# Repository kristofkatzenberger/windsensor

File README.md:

# Portable Wind Sensor based on MEMS Pressure Sensors

This repository contains the design files for a portable wind sensor developed in 2025/26 at the University of Applied Sciences Technikum Wien. This project was completed as part of the Bachelor's Thesis:

"Entwicklung eines tragbaren Windsensors auf Basis von MEMS-Drucksensoren"
(Development of a Portable Wind Sensor Based on MEMS Pressure Sensors)

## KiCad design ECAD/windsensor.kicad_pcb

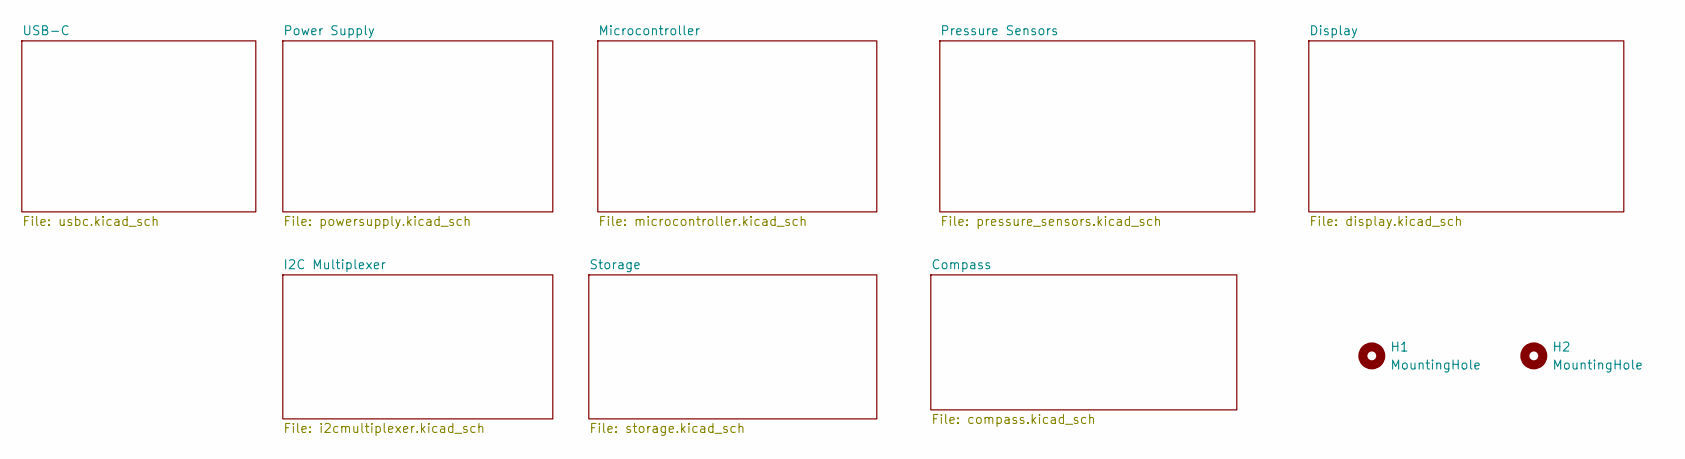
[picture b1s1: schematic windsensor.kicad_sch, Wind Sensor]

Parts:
H1, H2: MountingHole; MountingHole_3.2mm_M3

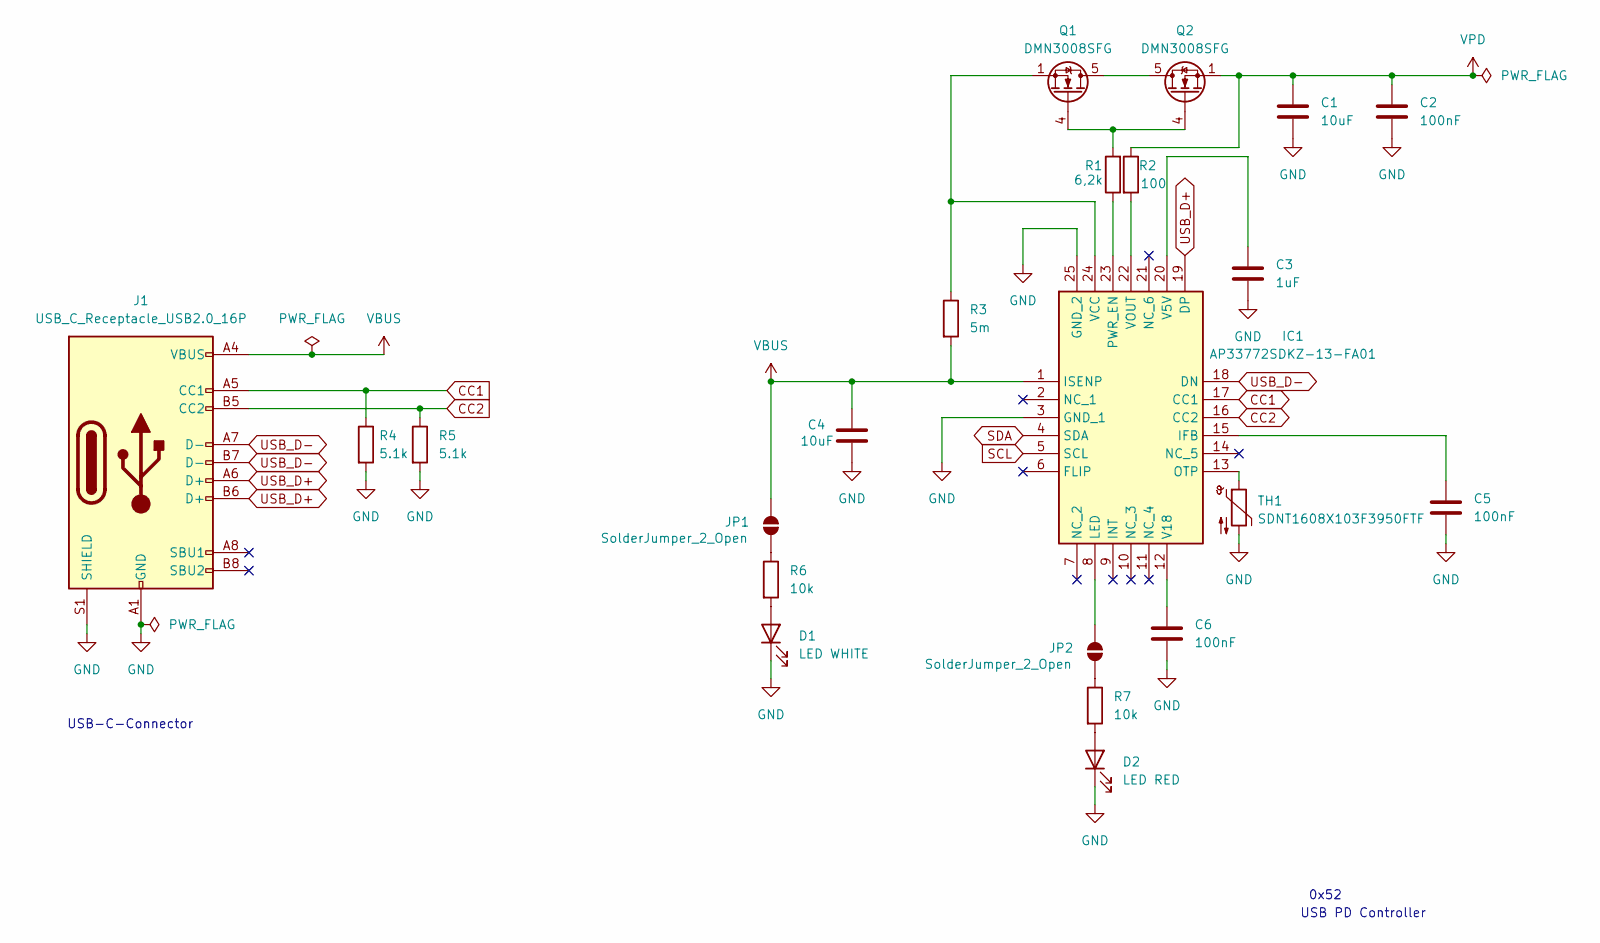
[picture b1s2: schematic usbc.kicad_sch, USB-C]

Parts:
C1, C4: 10uF; C_0402_1005Metric
C2, C5, C6: 100nF; C_0402_1005Metric
C3: 1uF; C_0402_1005Metric
D1: LED WHITE; LED_0603_1608Metric
D2: LED RED; LED_0603_1608Metric
IC1: AP33772SDKZ-13-FA01; AP33772SDKZ13FA01; Manufacturer_Part_Number AP33772SDKZ-13-FA01; Mouser Part Number 621-P33772SDKZ13FA01
J1: USB_C_Receptacle_USB2.0_16P; USB_C_Receptacle_GCT_USB4105-xx-A_16P_TopMnt_Horizontal
JP1, JP2: SolderJumper_2_Open; SolderJumper-2_P1.3mm_Open_TrianglePad1.0x1.5mm
Q1, Q2: DMN3008SFG; Diodes_PowerDI3333-8
R1: 6,2k; R_0402_1005Metric
R2: 100; R_0402_1005Metric
R3: 5m; R_1206_3216Metric; Tolerance 1%
R4, R5: 5.1k; R_0402_1005Metric
R6, R7: 10k; R_0402_1005Metric
TH1: SDNT1608X103F3950FTF; R_0603_1608Metric

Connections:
CC1: IC1.17 (CC1), J1.A5 (CC1), R4.1
CC2: IC1.16 (CC2), J1.B5 (CC2), R5.1
GND: C1.2, C2.2, C3.2, C4.2, C5.2, C6.2, D1.1 (K), D2.1 (K), IC1.3 (GND_1), IC1.25 (GND_2), J1.A1 (GND), J1.A12 (GND), J1.B1 (GND), J1.B12 (GND), J1.S1 (SHIELD), R4.2, R5.2, TH1.2; also elsewhere on the board
unnamed: D1.2 (A), R6.2
unnamed: D2.2 (A), R7.2
unnamed: C5.1, IC1.15 (IFB)
unnamed: IC1.8 (LED), JP2.1 (A)
unnamed: IC1.13 (OTP), TH1.1
unnamed: IC1.23 (PWR_EN), R1.1
unnamed: C3.1, IC1.20 (V5V)
unnamed: C6.1, IC1.12 (V18)
unnamed: IC1.24 (VCC), Q1.1 (S), Q1.2 (S), Q1.3 (S), R3.1
unnamed: IC1.22 (VOUT), R2.2
unnamed: JP1.2 (B), R6.1
unnamed: JP2.2 (B), R7.1
unnamed: Q1.5 (D), Q2.5 (D)
unnamed: Q1.4 (G), Q2.4 (G), R1.2
SCL: IC1.5 (SCL); also elsewhere on the board
SDA: IC1.4 (SDA); also elsewhere on the board
USB_D+: IC1.19 (DP), J1.A6 (D+), J1.B6 (D+); also elsewhere on the board
USB_D-: IC1.18 (DN), J1.A7 (D-), J1.B7 (D-); also elsewhere on the board
VBUS: C4.1, IC1.1 (ISENP), J1.A4 (VBUS), J1.A9 (VBUS), J1.B4 (VBUS), J1.B9 (VBUS), JP1.1 (A), R3.2
VPD: C1.1, C2.1, Q2.1 (S), Q2.2 (S), Q2.3 (S), R2.1; also elsewhere on the board

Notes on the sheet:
USB PD Controller
USB-C-Connector
0x52

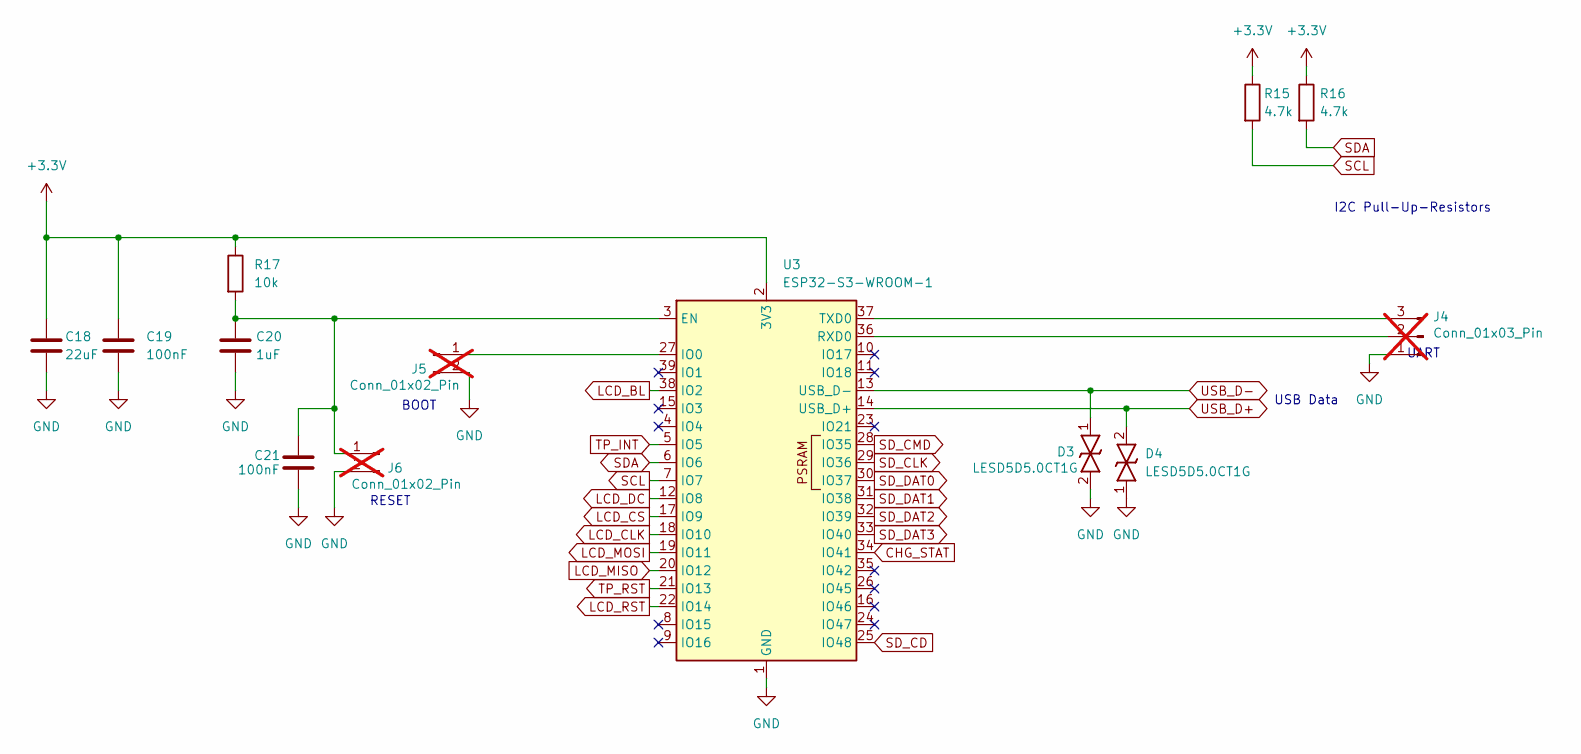
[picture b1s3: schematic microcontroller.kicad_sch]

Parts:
C18: 22uF; C_0402_1005Metric
C19, C21: 100nF; C_0402_1005Metric
C20: 1uF; C_0402_1005Metric
D3, D4: LESD5D5.0CT1G; LESD5D50CT1G; Manufacturer_Part_Number LESD5D5.0CT1G
J4: Conn_01x03_Pin; PinHeader_1x03_P2.54mm_Vertical; not fitted
J5, J6: Conn_01x02_Pin; PinHeader_1x02_P2.54mm_Vertical; not fitted
R15, R16: 4.7k; R_0402_1005Metric
R17: 10k; R_0402_1005Metric
U3: ESP32-S3-WROOM-1

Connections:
+3.3V: C18.1, C19.1, R15.1, R16.1, R17.1, U3.2 (3V3); also elsewhere on the board
CHG_STAT: U3.34 (IO41); also elsewhere on the board
GND: C18.2, C19.2, C20.2, C21.2, D3.2, D4.1, J4.1, J5.2, J6.2, U3.1 (GND), U3.40 (GND), U3.41 (GND); also elsewhere on the board
LCD_BL: U3.38 (IO2); also elsewhere on the board
LCD_CLK: U3.18 (IO10); also elsewhere on the board
LCD_CS: U3.17 (IO9); also elsewhere on the board
LCD_DC: U3.12 (IO8); also elsewhere on the board
LCD_MISO: U3.20 (IO12); also elsewhere on the board
LCD_MOSI: U3.19 (IO11); also elsewhere on the board
LCD_RST: U3.22 (IO14); also elsewhere on the board
unnamed: J4.2, U3.36 (RXD0)
unnamed: J4.3, U3.37 (TXD0)
unnamed: J5.1, U3.27 (IO0)
unnamed: C20.1, C21.1, J6.1, R17.2, U3.3 (EN)
SCL: R15.2, U3.7 (IO7); also elsewhere on the board
SDA: R16.2, U3.6 (IO6); also elsewhere on the board
SD_CD: U3.25 (IO48); also elsewhere on the board
SD_CLK: U3.29 (IO36); also elsewhere on the board
SD_CMD: U3.28 (IO35); also elsewhere on the board
SD_DAT0: U3.30 (IO37); also elsewhere on the board
SD_DAT1: U3.31 (IO38); also elsewhere on the board
SD_DAT2: U3.32 (IO39); also elsewhere on the board
SD_DAT3: U3.33 (IO40); also elsewhere on the board
TP_INT: U3.5 (IO5); also elsewhere on the board
TP_RST: U3.21 (IO13); also elsewhere on the board
USB_D+: D4.2, U3.14 (USB_D+); also elsewhere on the board
USB_D-: D3.1, U3.13 (USB_D-); also elsewhere on the board

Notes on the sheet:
I2C Pull-Up-Resistors
UART
USB Data
BOOT
RESET

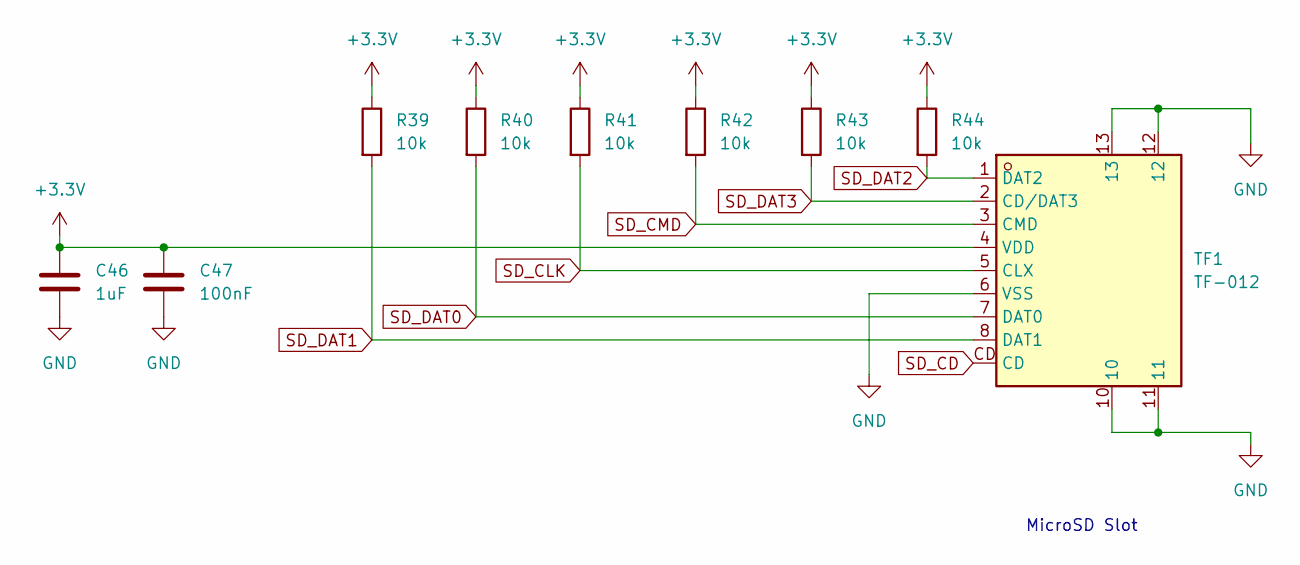
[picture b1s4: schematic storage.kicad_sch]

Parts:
C46: 1uF; C_0402_1005Metric
C47: 100nF; C_0402_1005Metric
R39, R40, R41, R42, R43, R44: 10k; R_0402_1005Metric
TF1: TF-012; TF-SMD_TF-012; Manufacturer Part TF-012; LCSC Part Name 自弹式 MicroSD卡(TF卡) 卡座

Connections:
+3.3V: C46.1, C47.1, R39.1, R40.1, R41.1, R42.1, R43.1, R44.1, TF1.4 (VDD); also elsewhere on the board
GND: C46.2, C47.2, TF1.6 (VSS), TF1.10, TF1.11, TF1.12, TF1.13; also elsewhere on the board
SD_CD: TF1.CD; also elsewhere on the board
SD_CLK: R41.2, TF1.5 (CLX); also elsewhere on the board
SD_CMD: R42.2, TF1.3 (CMD); also elsewhere on the board
SD_DAT0: R40.2, TF1.7 (DAT0); also elsewhere on the board
SD_DAT1: R39.2, TF1.8 (DAT1); also elsewhere on the board
SD_DAT2: R44.2, TF1.1 (DAT2); also elsewhere on the board
SD_DAT3: R43.2, TF1.2 (CD/DAT3); also elsewhere on the board

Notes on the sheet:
MicroSD Slot

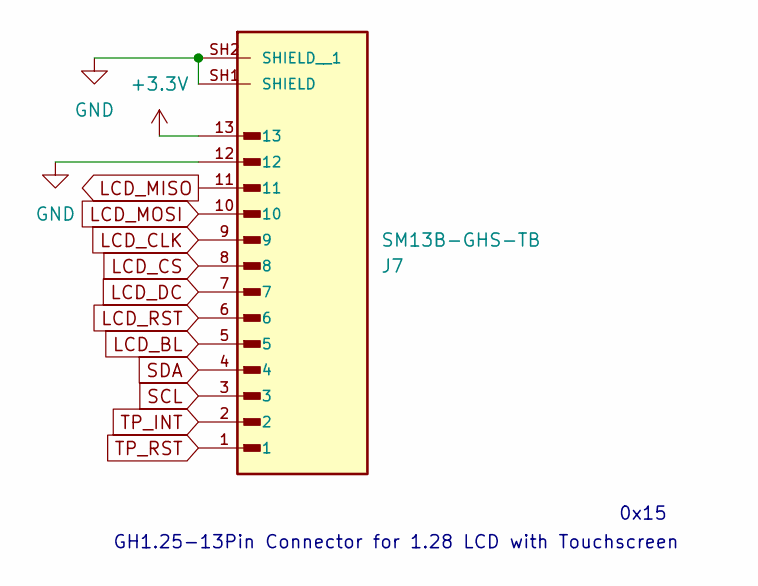
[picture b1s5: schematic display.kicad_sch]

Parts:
J7: SM13B-GHS-TB; JST_SM13B-GHS-TB; PARTREV 18/3/21

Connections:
+3.3V: J7.13; also elsewhere on the board
GND: J7.12, J7.SH1 (SHIELD), J7.SH2 (SHIELD__1); also elsewhere on the board
LCD_BL: J7.5; also elsewhere on the board
LCD_CLK: J7.9; also elsewhere on the board
LCD_CS: J7.8; also elsewhere on the board
LCD_DC: J7.7; also elsewhere on the board
LCD_MISO: J7.11; also elsewhere on the board
LCD_MOSI: J7.10; also elsewhere on the board
LCD_RST: J7.6; also elsewhere on the board
SCL: J7.3; also elsewhere on the board
SDA: J7.4; also elsewhere on the board
TP_INT: J7.2; also elsewhere on the board
TP_RST: J7.1; also elsewhere on the board

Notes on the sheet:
GH1.25-13Pin Connector for 1.28 LCD with Touchscreen
0x15

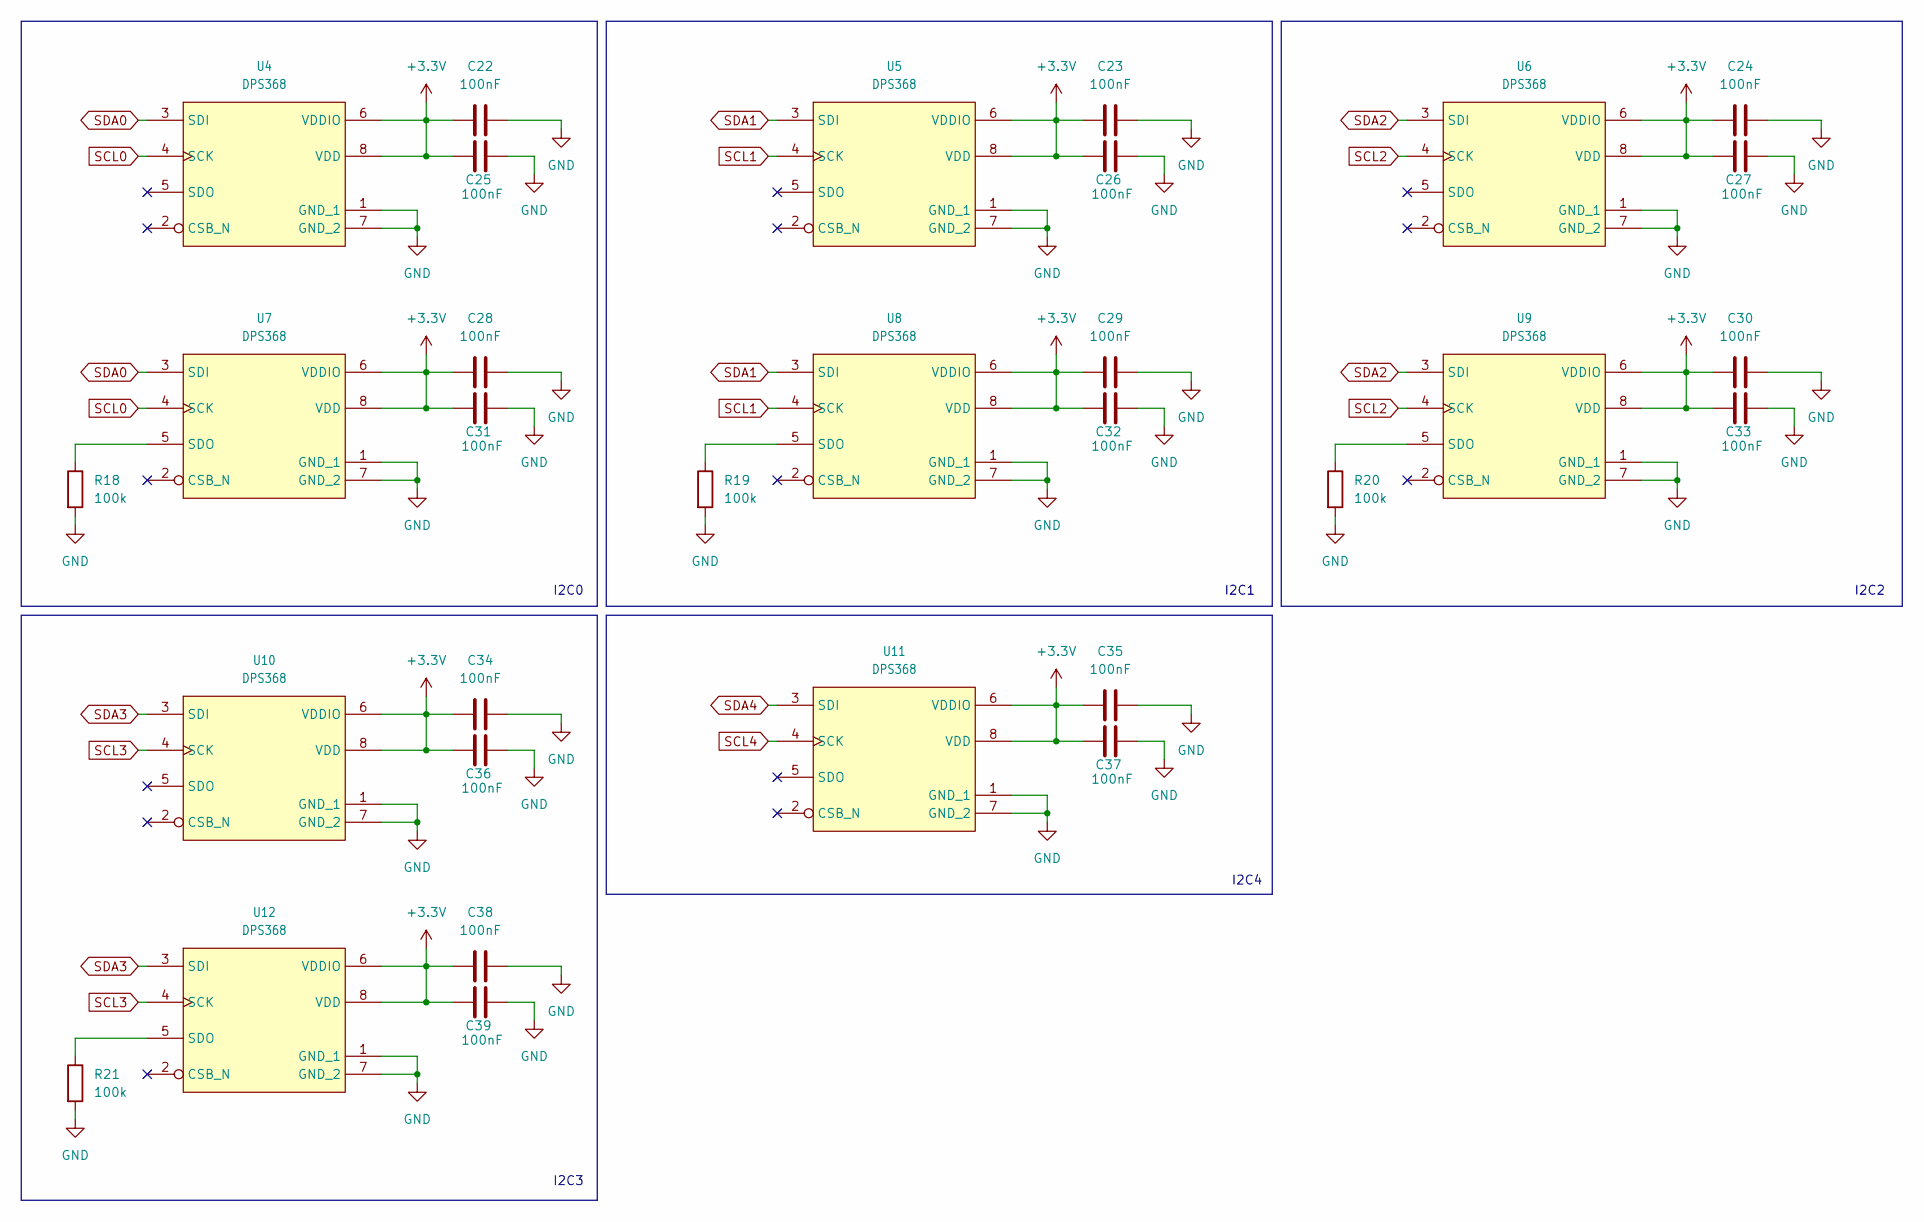
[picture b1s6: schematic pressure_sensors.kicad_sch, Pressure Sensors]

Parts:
C22, C23, C24, C25, C26, C27, C28, C29, C30, C31, C32, C33, C34, C35, C36, C37, C38, C39: 100nF; C_0402_1005Metric
R18, R19, R20, R21: 100k; R_0402_1005Metric
U4, U5, U6, U7, U8, U9, U10, U11, U12: DPS368; LGA8S145X65P2X4_200X250X110-V

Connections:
+3.3V: C22.1, C23.1, C24.1, C25.1, C26.1, C27.1, C28.1, C29.1, C30.1, C31.1, C32.1, C33.1, C34.1, C35.1, C36.1, C37.1, C38.1, C39.1, U4.6 (VDDIO), U4.8 (VDD), U5.6 (VDDIO), U5.8 (VDD), U6.6 (VDDIO), U6.8 (VDD), U7.6 (VDDIO), U7.8 (VDD), U8.6 (VDDIO), U8.8 (VDD), U9.6 (VDDIO), U9.8 (VDD), U10.6 (VDDIO), U10.8 (VDD), U11.6 (VDDIO), U11.8 (VDD), U12.6 (VDDIO), U12.8 (VDD); also elsewhere on the board
GND: C22.2, C23.2, C24.2, C25.2, C26.2, C27.2, C28.2, C29.2, C30.2, C31.2, C32.2, C33.2, C34.2, C35.2, C36.2, C37.2, C38.2, C39.2, R18.2, R19.2, R20.2, R21.2, U4.1 (GND_1), U4.7 (GND_2), U5.1 (GND_1), U5.7 (GND_2), U6.1 (GND_1), U6.7 (GND_2), U7.1 (GND_1), U7.7 (GND_2), U8.1 (GND_1), U8.7 (GND_2), U9.1 (GND_1), U9.7 (GND_2), U10.1 (GND_1), U10.7 (GND_2), U11.1 (GND_1), U11.7 (GND_2), U12.1 (GND_1), U12.7 (GND_2); also elsewhere on the board
unnamed: R18.1, U7.5 (SDO)
unnamed: R19.1, U8.5 (SDO)
unnamed: R20.1, U9.5 (SDO)
unnamed: R21.1, U12.5 (SDO)
SCL0: U4.4 (SCK), U7.4 (SCK); also elsewhere on the board
SCL1: U5.4 (SCK), U8.4 (SCK); also elsewhere on the board
SCL2: U6.4 (SCK), U9.4 (SCK); also elsewhere on the board
SCL3: U10.4 (SCK), U12.4 (SCK); also elsewhere on the board
SCL4: U11.4 (SCK); also elsewhere on the board
SDA0: U4.3 (SDI), U7.3 (SDI); also elsewhere on the board
SDA1: U5.3 (SDI), U8.3 (SDI); also elsewhere on the board
SDA2: U6.3 (SDI), U9.3 (SDI); also elsewhere on the board
SDA3: U10.3 (SDI), U12.3 (SDI); also elsewhere on the board
SDA4: U11.3 (SDI); also elsewhere on the board

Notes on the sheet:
I2C3
I2C2
I2C4
I2C1
I2C0

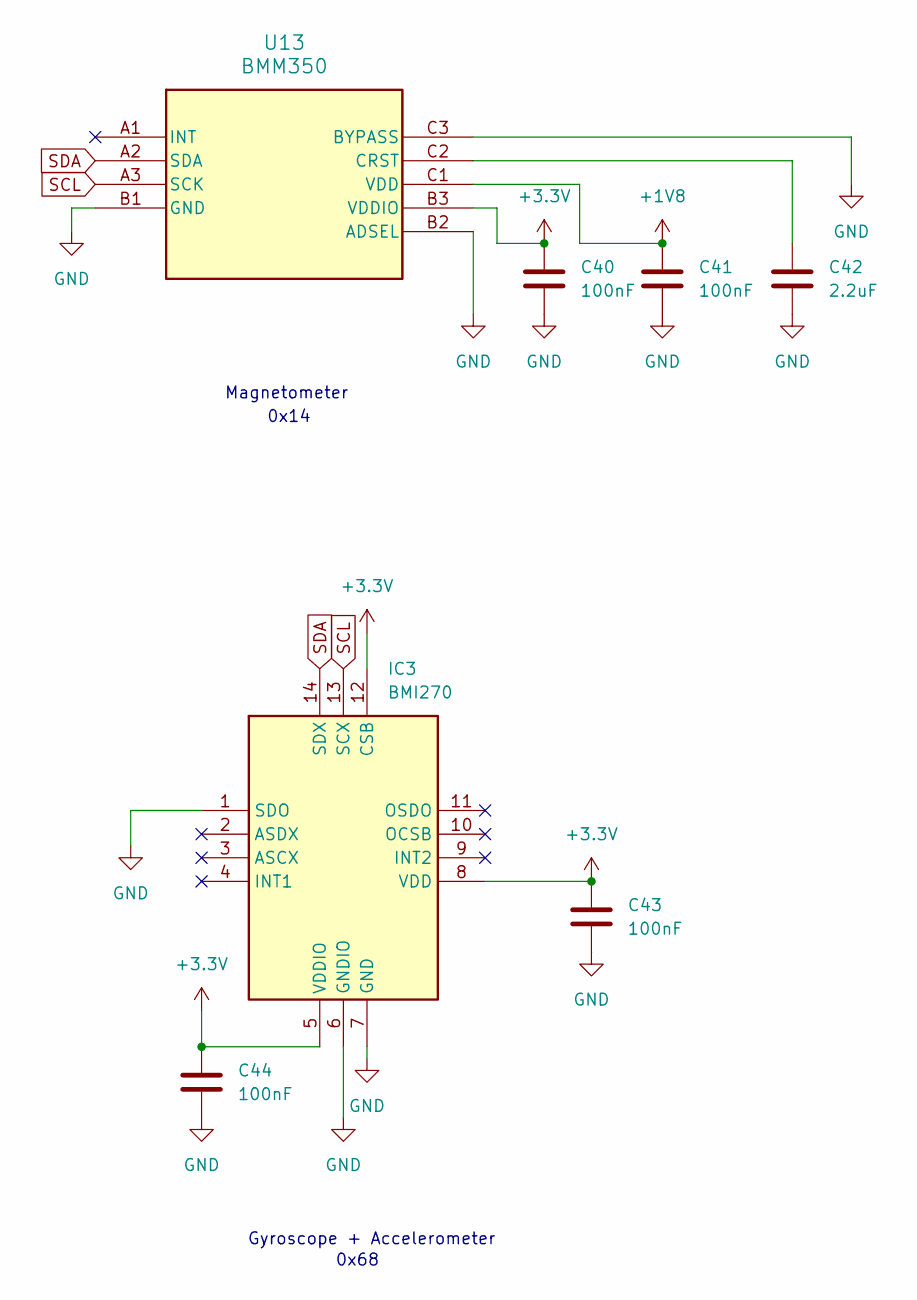
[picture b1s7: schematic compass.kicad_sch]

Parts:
C40, C41, C43: 100nF; C_0402_1005Metric
C42: 2.2uF; C_0402_1005Metric
C44: 100nF; C_0402_1005Metric_Pad0.74x0.62mm_HandSolder
IC3: BMI270; Mouser Part Number 262-BMI270
U13: BMM350; BGA9_BMM350_BOS

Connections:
+1V8: C41.1, U13.C1 (VDD); also elsewhere on the board
+3.3V: C40.1, C43.1, C44.1, IC3.5 (VDDIO), IC3.8 (VDD), IC3.12 (CSB), U13.B3 (VDDIO); also elsewhere on the board
GND: C40.2, C41.2, C42.1, C43.2, C44.2, IC3.1 (SDO), IC3.6 (GNDIO), IC3.7 (GND), U13.B1 (GND), U13.B2 (ADSEL), U13.C3 (BYPASS); also elsewhere on the board
unnamed: C42.2, U13.C2 (CRST)
SCL: IC3.13 (SCX), U13.A3 (SCK); also elsewhere on the board
SDA: IC3.14 (SDX), U13.A2 (SDA); also elsewhere on the board

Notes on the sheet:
Gyroscope + Accelerometer
Magnetometer
0x14
0x68

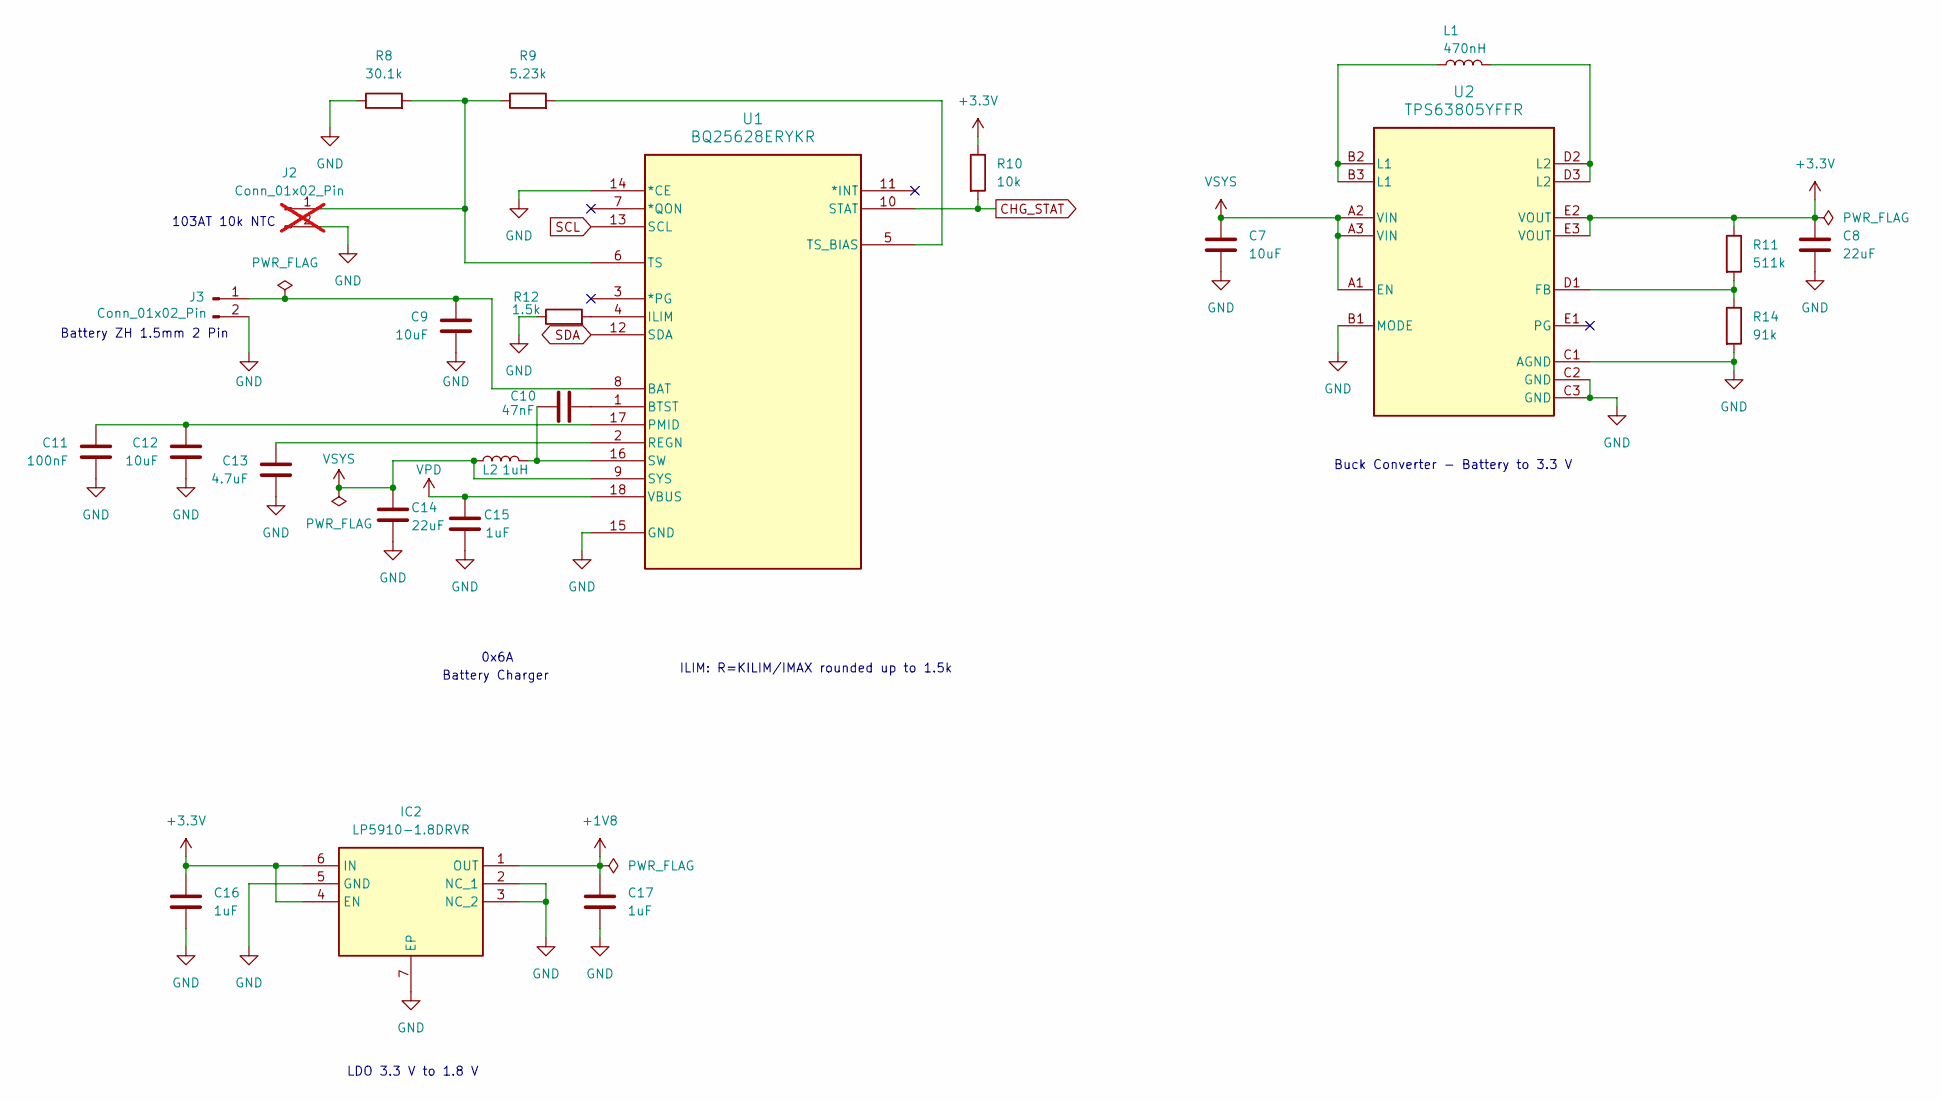
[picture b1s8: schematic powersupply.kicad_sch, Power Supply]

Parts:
C7, C9, C12: 10uF; C_0402_1005Metric
C8, C14: 22uF; C_0402_1005Metric
C10: 47nF; C_0402_1005Metric
C11: 100nF; C_0402_1005Metric
C13: 4.7uF; C_0402_1005Metric
C15, C16, C17: 1uF; C_0402_1005Metric
IC2: LP5910-1.8DRVR; SON65P200X200X80-7N; Mouser Part Number 595-LP5910-1.8DRVR
J2: Conn_01x02_Pin; PinHeader_1x02_P2.54mm_Vertical; not fitted
J3: Conn_01x02_Pin; JST_ZH_B2B-ZR-SM4-TF_1x02-1MP_P1.50mm_Vertical
L1: 470nH; L_Murata_DFE201610P
L2: 1uH; L_1008_2520Metric
R8: 30.1k; R_0402_1005Metric
R9: 5.23k; R_0402_1005Metric
R10: 10k; R_0402_1005Metric
R11: 511k; R_0402_1005Metric
R12: 1.5k; R_0402_1005Metric
R14: 91k; R_0402_1005Metric
U1: BQ25628ERYKR; WQFN-HR18__RYK_TEX
U2: TPS63805YFFR; YFF0015AHAN

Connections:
+1V8: C17.1, IC2.1 (OUT); also elsewhere on the board
+3.3V: C8.1, C16.1, IC2.4 (EN), IC2.6 (IN), R10.1, R11.1, U2.E2 (VOUT), U2.E3 (VOUT); also elsewhere on the board
CHG_STAT: R10.2, U1.10 (STAT); also elsewhere on the board
GND: C7.2, C8.2, C9.1, C11.1, C12.1, C13.1, C14.1, C15.1, C16.2, C17.2, IC2.2 (NC_1), IC2.3 (NC_2), IC2.5 (GND), IC2.7 (EP), J2.2, J3.2, R8.1, R12.1, R14.2, U1.14 (*CE), U1.15 (GND), U2.B1 (MODE), U2.C1 (AGND), U2.C2 (GND), U2.C3 (GND); also elsewhere on the board
unnamed: J2.1, R8.2, R9.1, U1.6 (TS)
unnamed: C9.2, J3.1, U1.8 (BAT)
unnamed: L1.1, U2.D2 (L2), U2.D3 (L2)
unnamed: L1.2, U2.B2 (L1), U2.B3 (L1)
unnamed: C10.1, U1.1 (BTST)
unnamed: R12.2, U1.4 (ILIM)
unnamed: C11.2, C12.2, U1.17 (PMID)
unnamed: C13.2, U1.2 (REGN)
unnamed: C10.2, L2.2, U1.16 (SW)
unnamed: R9.2, U1.5 (TS_BIAS)
unnamed: R11.2, R14.1, U2.D1 (FB)
SCL: U1.13 (SCL); also elsewhere on the board
SDA: U1.12 (SDA); also elsewhere on the board
VPD: C15.2, U1.18 (VBUS); also elsewhere on the board
VSYS: C7.1, C14.2, L2.1, U1.9 (SYS), U2.A1 (EN), U2.A2 (VIN), U2.A3 (VIN)

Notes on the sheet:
Battery Charger
Battery ZH 1.5mm 2 Pin
ILIM: R=KILIM/IMAX rounded up to 1.5k
103AT 10k NTC
0x6A
LDO 3.3 V to 1.8 V
Buck Converter - Battery to 3.3 V

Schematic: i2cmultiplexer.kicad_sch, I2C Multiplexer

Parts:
C45: 100nF; C_0402_1005Metric
R22, R23, R24, R25, R26, R27, R28, R29, R30, R31: 4.7k; R_0402_1005Metric
R32: 10k; R_0402_1005Metric
R33, R34, R35, R36, R37, R38: 50; R_0402_1005Metric
U14: TCA9548APWR; TSSOP-24_4.4x7.8mm_P0.65mm

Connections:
+3.3V: C45.2, R22.1, R23.1, R24.1, R25.1, R26.1, R27.1, R28.1, R29.1, R30.1, R31.1, R32.1, U14.24 (VCC); also elsewhere on the board
GND: C45.1, R33.2, R34.2, R35.2, R36.2, R37.2, R38.2, U14.1 (A0), U14.2 (A1), U14.12 (GND), U14.21 (A2); also elsewhere on the board
unnamed: R38.1, U14.16 (SC5)
unnamed: R36.1, U14.18 (SC6)
unnamed: R34.1, U14.20 (SC7)
unnamed: R37.1, U14.15 (SD5)
unnamed: R35.1, U14.17 (SD6)
unnamed: R33.1, U14.19 (SD7)
unnamed: R32.2, U14.3 (~RESET)
SCL: U14.22 (SCL); also elsewhere on the board
SCL0: R22.2, U14.5 (SC0); also elsewhere on the board
SCL1: R24.2, U14.7 (SC1); also elsewhere on the board
SCL2: R26.2, U14.9 (SC2); also elsewhere on the board
SCL3: R28.2, U14.11 (SC3); also elsewhere on the board
SCL4: R30.2, U14.14 (SC4); also elsewhere on the board
SDA: U14.23 (SDA); also elsewhere on the board
SDA0: R23.2, U14.4 (SD0); also elsewhere on the board
SDA1: R25.2, U14.6 (SD1); also elsewhere on the board
SDA2: R27.2, U14.8 (SD2); also elsewhere on the board
SDA3: R29.2, U14.10 (SD3); also elsewhere on the board
SDA4: R31.2, U14.13 (SD4); also elsewhere on the board

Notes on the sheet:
0x70

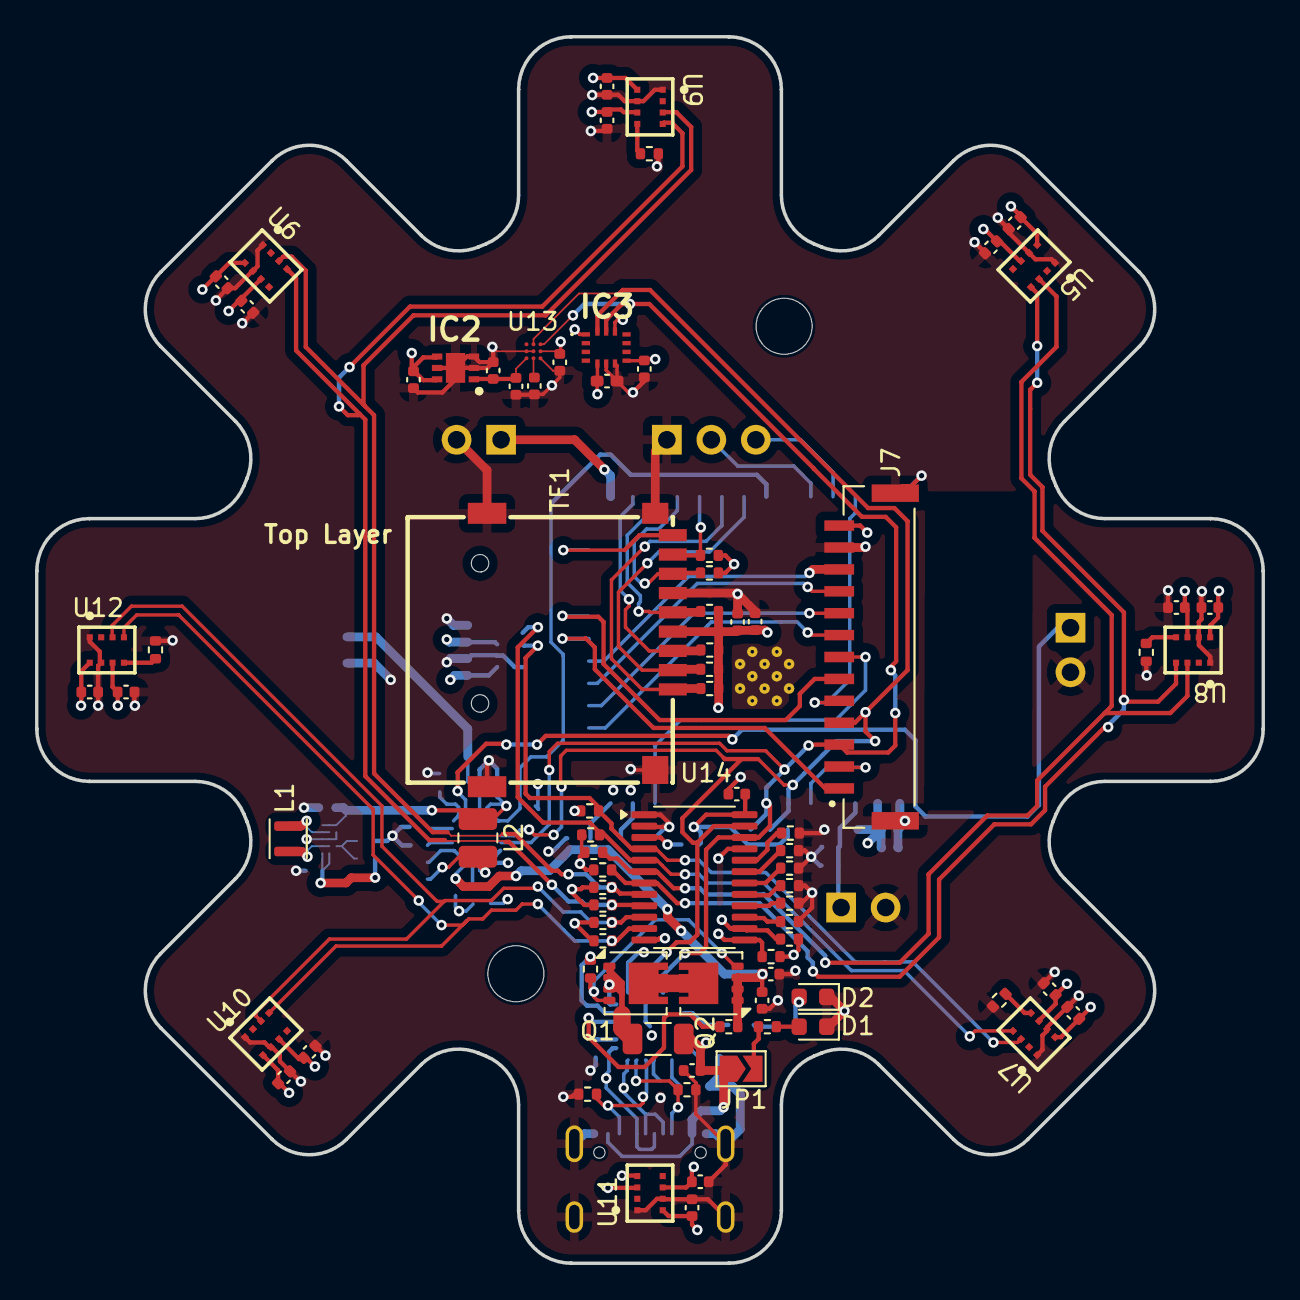
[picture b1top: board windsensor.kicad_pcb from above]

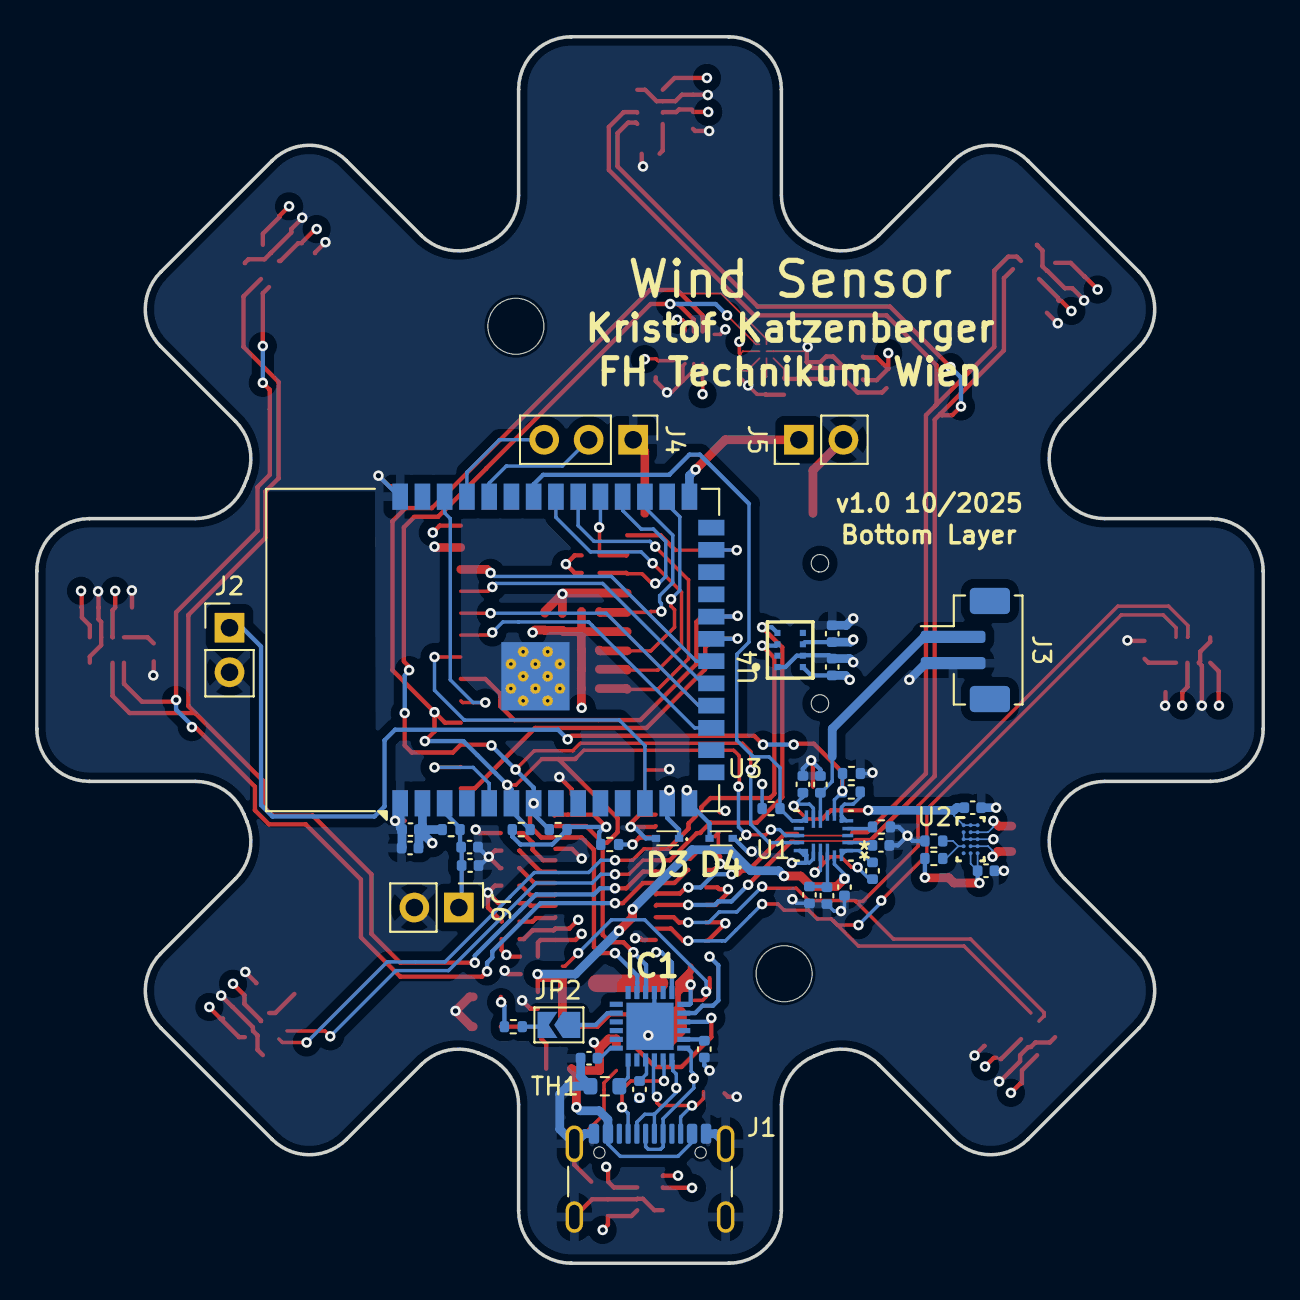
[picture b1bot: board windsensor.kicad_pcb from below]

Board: 4 copper layers, 70.0 x 70.0 mm, 128 parts (44 on the bottom side), 80 nets.

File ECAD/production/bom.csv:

Designator,Footprint,Quantity,Value,LCSC Part #
"C1, C12, C4, C7, C9",0402,5,10uF,
C10,0402,1,47nF,
"C11, C19, C2, C21, C22, C23, C24, C25, C26, C27, C28, C29, C30, C31, C32, C33, C34, C35, C36, C37, C38, C39, C40, C41, C43, C44, C45, C47, C5, C6",0402,30,100nF,
C13,0402,1,4.7uF,
C14,0402,1,20uF,
"C15, C16, C17, C20, C3, C46",0402,6,1uF,
"C18, C8",0402,2,22uF,
C42,0402,1,2.2uF,
D1,0603,1,LED WHITE,
D2,0603,1,LED RED,
"D3, D4",LESD5D50CT1G,2,LESD5D5.0CT1G,
IC1,AP33772SDKZ13FA01,1,AP33772SDKZ-13-FA01,
IC2,SON65P200X200X80-7N,1,LP5910-1.8DRVR,
IC3,BMI270,1,BMI270,
J1,USB_C_Receptacle_GCT_USB4105-xx-A_16P_TopMnt_Horizontal,1,USB_C_Receptacle_USB2.0_16P,
J3,JST_ZH_B2B-ZR-SM4-TF_1x02-1MP_P1.50mm_Vertical,1,Conn_01x02_Pin,
J7,JST_SM13B-GHS-TB,1,SM13B-GHS-TB,
L1,L_Murata_DFE201610P,1,470nH,
L2,1008,1,1uH,
"Q1, Q2",Diodes_PowerDI3333-8,2,DMN3008SFG,
R1,0402,1,"6,2k",
"R10, R17, R32, R39, R40, R41, R42, R43, R44, R6, R7",0402,11,10k,
R11,0402,1,511k,
R12,0402,1,1.5k,
R14,0402,1,91k,
"R15, R16, R22, R23, R24, R25, R26, R27, R28, R29, R30, R31",0402,12,4.7k,
"R18, R19, R20, R21",0402,4,100k,
R2,0402,1,100,
R3,1206,1,5m,
"R33, R34, R35, R36, R37, R38",0402,6,50,
"R4, R5",0402,2,5.1k,
R8,0402,1,30.1k,
R9,0402,1,5.23k,
TF1,TF-SMD_TF-012,1,TF-012,
TH1,0603,1,SDNT1608X103F3950FTF,
U1,WQFN-HR18__RYK_TEX,1,BQ25628ERYKR,
"U10, U11, U12, U4, U5, U6, U7, U8, U9",LGA8S145X65P2X4_200X250X110-V,9,DPS368,
U13,BGA9_BMM350_BOS,1,BMM350,
U14,TSSOP-24_4.4x7.8mm_P0.65mm,1,TCA9548APWR,
U2,YFF0015AHAN,1,TPS63805YFFR,
U3,ESP32-S3-WROOM-1,1,ESP32-S3-WROOM-1,

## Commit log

2026-05-04 add README
2026-05-04 add subdirectories
2026-05-04 Remove .DS_Store files from repository
2026-05-04 add ECAD files
2026-05-04 add MCAD files
2026-05-04 add Software
